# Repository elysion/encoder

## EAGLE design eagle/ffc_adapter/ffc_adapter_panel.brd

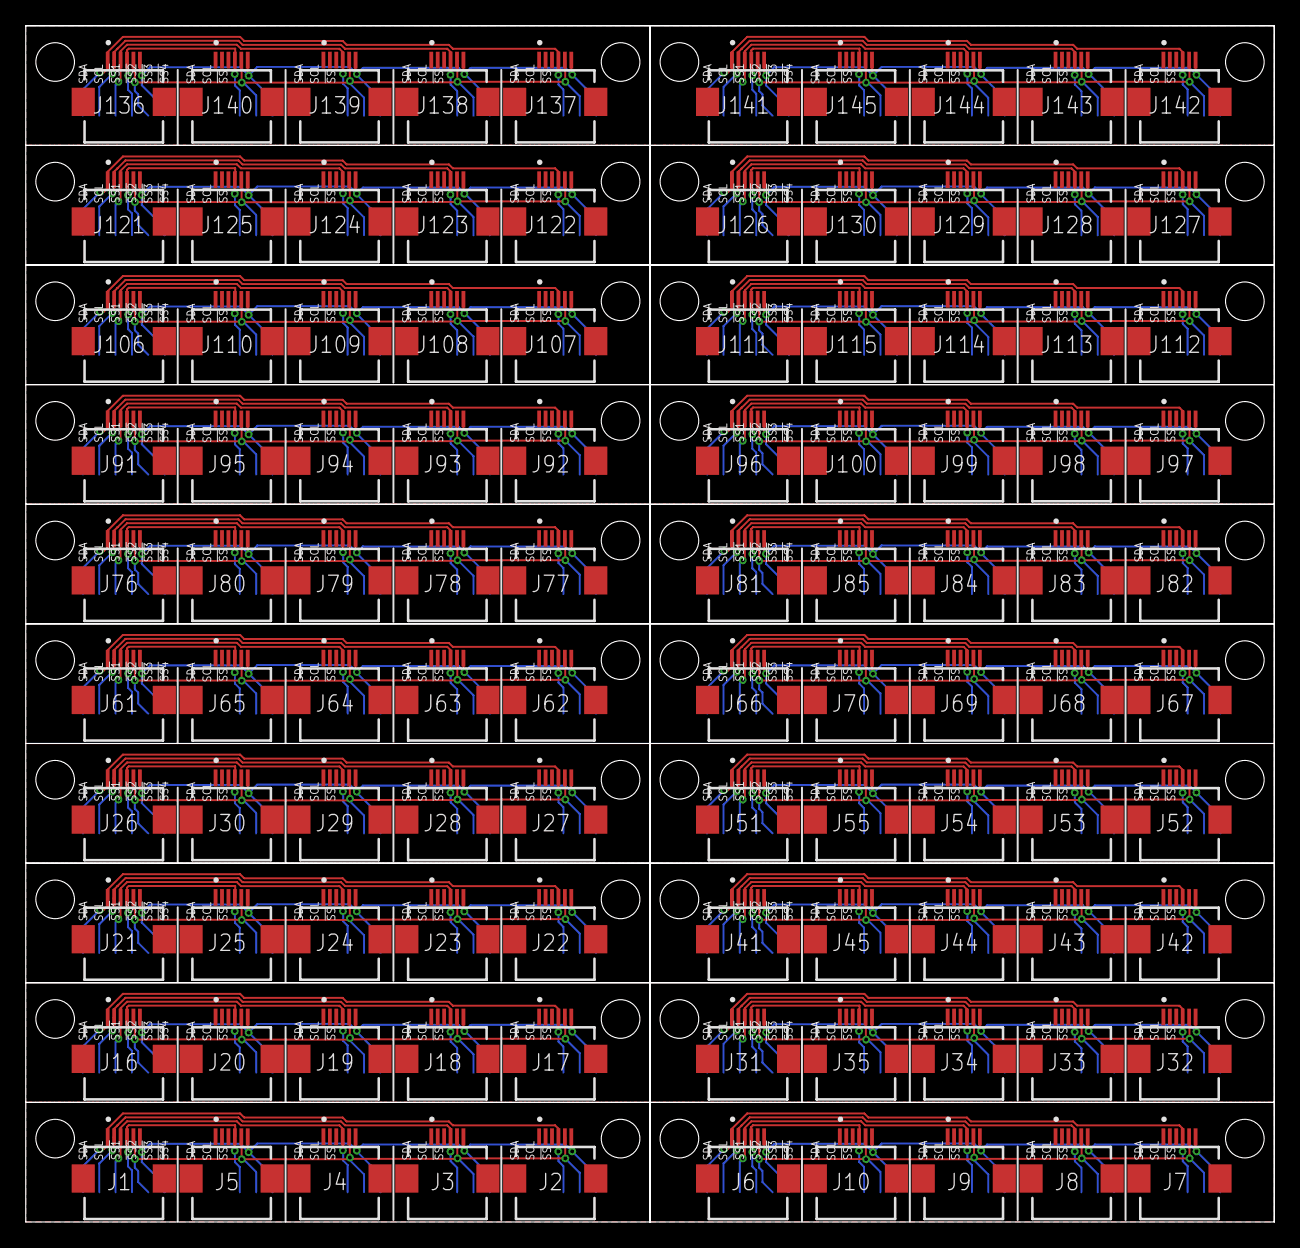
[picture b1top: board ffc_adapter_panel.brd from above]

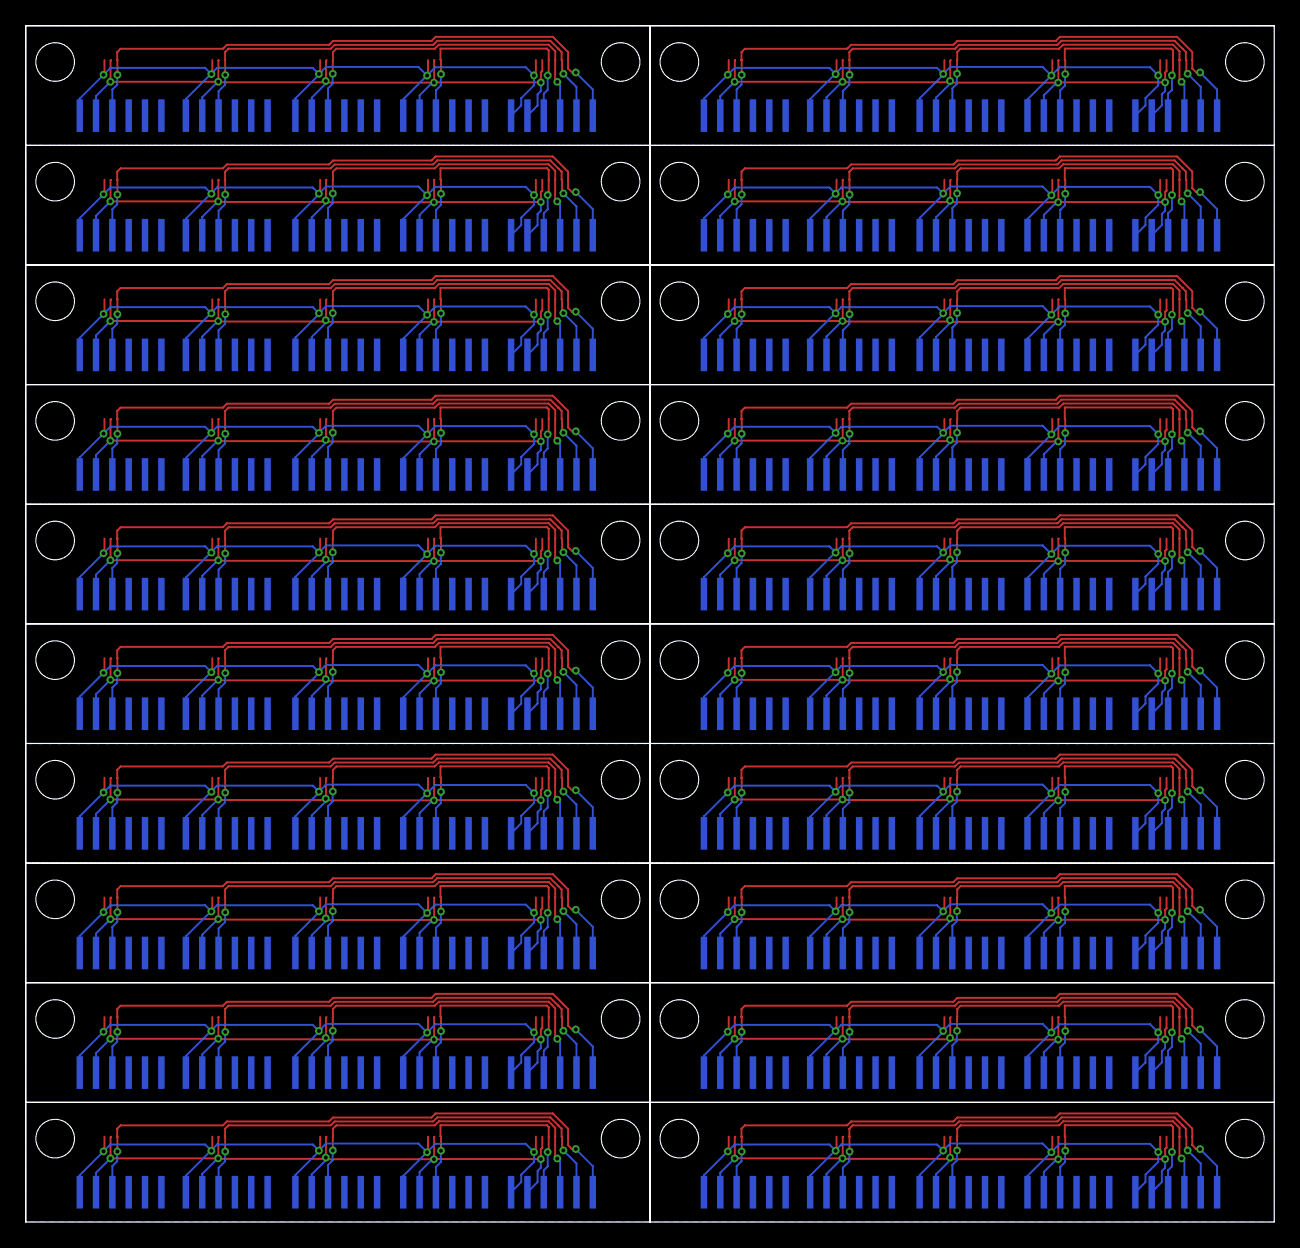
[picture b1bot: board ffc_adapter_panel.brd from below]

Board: 2 copper layers, 97.0 x 93.0 mm, 200 parts (100 on the bottom side), 120 nets.

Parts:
J1, J2, J3, J4, J5, J6, J7, J8, J9, J10, J16, J17, J18, J19, J20, J21, J22, J23, J24, J25, J26, J27, J28, J29, J30, J31, J32, J33, J34, J35, J41, J42, J43, J44, J45, J51, J52, J53, J54, J55, J61, J62, J63, J64, J65, J66, J67, J68, J69, J70, J76, J77, J78, J79, J80, J81, J82, J83, J84, J85, J91, J92, J93, J94, J95, J96, J97, J98, J99, J100, J106, J107, J108, J109, J110, J111, J112, J113, J114, J115, J121, J122, J123, J124, J125, J126, J127, J128, J129, J130, J136, J137, J138, J139, J140, J141, J142, J143, J144, J145: FH12-6S-0.5SH(55); FH12-6S-0.5SH(55)_1
U$1, U$2, U$3, U$4, U$5, U$6, U$7, U$8, U$9, U$10, U$16, U$17, U$18, U$19, U$20, U$21, U$22, U$23, U$24, U$25, U$26, U$27, U$28, U$29, U$30, U$31, U$32, U$33, U$34, U$35, U$41, U$42, U$43, U$44, U$45, U$51, U$52, U$53, U$54, U$55, U$61, U$62, U$63, U$64, U$65, U$66, U$67, U$68, U$69, U$70, U$76, U$77, U$78, U$79, U$80, U$81, U$82, U$83, U$84, U$85, U$91, U$92, U$93, U$94, U$95, U$96, U$97, U$98, U$99, U$100, U$106, U$107, U$108, U$109, U$110, U$111, U$112, U$113, U$114, U$115, U$121, U$122, U$123, U$124, U$125, U$126, U$127, U$128, U$129, U$130, U$136, U$137, U$138, U$139, U$140, U$141, U$142, U$143, U$144, U$145: 6PIN_SOLDER_PAD

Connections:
!SS1: J1.4, J5.4, U$4.P$3, U$5.P$3
!SS2: J1.3, J4.4, U$3.P$3, U$4.P$4
!SS3: J1.2, J3.4, U$2.P$3, U$4.P$5
!SS4: J1.1, J2.4, U$1.P$3, U$4.P$6
!SS5: J6.4, J10.4, U$6.P$3, U$10.P$3
!SS6: J6.3, J9.4, U$6.P$4, U$9.P$3
!SS7: J6.2, J8.4, U$6.P$5, U$8.P$3
!SS8: J6.1, J7.4, U$6.P$6, U$7.P$3
!SS13: J16.4, J20.4, U$16.P$3, U$20.P$3
!SS14: J16.3, J19.4, U$16.P$4, U$19.P$3
!SS15: J16.2, J18.4, U$16.P$5, U$18.P$3
!SS16: J16.1, J17.4, U$16.P$6, U$17.P$3
!SS17: J21.4, J25.4, U$21.P$3, U$25.P$3
!SS18: J21.3, J24.4, U$21.P$4, U$24.P$3
!SS19: J21.2, J23.4, U$21.P$5, U$23.P$3
!SS20: J21.1, J22.4, U$21.P$6, U$22.P$3
!SS21: J26.4, J30.4, U$26.P$3, U$30.P$3
!SS22: J26.3, J29.4, U$26.P$4, U$29.P$3
!SS23: J26.2, J28.4, U$26.P$5, U$28.P$3
!SS24: J26.1, J27.4, U$26.P$6, U$27.P$3
!SS25: J31.4, J35.4, U$31.P$3, U$35.P$3
!SS26: J31.3, J34.4, U$31.P$4, U$34.P$3
!SS27: J31.2, J33.4, U$31.P$5, U$33.P$3
!SS28: J31.1, J32.4, U$31.P$6, U$32.P$3
!SS33: J41.4, J45.4, U$41.P$3, U$45.P$3
!SS34: J41.3, J44.4, U$41.P$4, U$44.P$3
!SS35: J41.2, J43.4, U$41.P$5, U$43.P$3
!SS36: J41.1, J42.4, U$41.P$6, U$42.P$3
!SS41: J51.4, J55.4, U$51.P$3, U$55.P$3
!SS42: J51.3, J54.4, U$51.P$4, U$54.P$3
!SS43: J51.2, J53.4, U$51.P$5, U$53.P$3
!SS44: J51.1, J52.4, U$51.P$6, U$52.P$3
!SS49: J61.4, J65.4, U$61.P$3, U$65.P$3
!SS50: J61.3, J64.4, U$61.P$4, U$64.P$3
!SS51: J61.2, J63.4, U$61.P$5, U$63.P$3
!SS52: J61.1, J62.4, U$61.P$6, U$62.P$3
!SS53: J66.4, J70.4, U$66.P$3, U$70.P$3
!SS54: J66.3, J69.4, U$66.P$4, U$69.P$3
!SS55: J66.2, J68.4, U$66.P$5, U$68.P$3
!SS56: J66.1, J67.4, U$66.P$6, U$67.P$3
!SS61: J76.4, J80.4, U$76.P$3, U$80.P$3
!SS62: J76.3, J79.4, U$76.P$4, U$79.P$3
!SS63: J76.2, J78.4, U$76.P$5, U$78.P$3
!SS64: J76.1, J77.4, U$76.P$6, U$77.P$3
!SS65: J81.4, J85.4, U$81.P$3, U$85.P$3
!SS66: J81.3, J84.4, U$81.P$4, U$84.P$3
!SS67: J81.2, J83.4, U$81.P$5, U$83.P$3
!SS68: J81.1, J82.4, U$81.P$6, U$82.P$3
!SS73: J91.4, J95.4, U$91.P$3, U$95.P$3
!SS74: J91.3, J94.4, U$91.P$4, U$94.P$3
!SS75: J91.2, J93.4, U$91.P$5, U$93.P$3
!SS76: J91.1, J92.4, U$91.P$6, U$92.P$3
!SS77: J96.4, J100.4, U$96.P$3, U$100.P$3
!SS78: J96.3, J99.4, U$96.P$4, U$99.P$3
!SS79: J96.2, J98.4, U$96.P$5, U$98.P$3
!SS80: J96.1, J97.4, U$96.P$6, U$97.P$3
!SS85: J106.4, J110.4, U$106.P$3, U$110.P$3
!SS86: J106.3, J109.4, U$106.P$4, U$109.P$3
!SS87: J106.2, J108.4, U$106.P$5, U$108.P$3
!SS88: J106.1, J107.4, U$106.P$6, U$107.P$3
!SS89: J111.4, J115.4, U$111.P$3, U$115.P$3
!SS90: J111.3, J114.4, U$111.P$4, U$114.P$3
!SS91: J111.2, J113.4, U$111.P$5, U$113.P$3
!SS92: J111.1, J112.4, U$111.P$6, U$112.P$3
!SS97: J121.4, J125.4, U$121.P$3, U$125.P$3
!SS98: J121.3, J124.4, U$121.P$4, U$124.P$3
!SS99: J121.2, J123.4, U$121.P$5, U$123.P$3
!SS100: J121.1, J122.4, U$121.P$6, U$122.P$3
!SS101: J126.4, J130.4, U$126.P$3, U$130.P$3
!SS102: J126.3, J129.4, U$126.P$4, U$129.P$3
!SS103: J126.2, J128.4, U$126.P$5, U$128.P$3
!SS104: J126.1, J127.4, U$126.P$6, U$127.P$3
!SS109: J136.4, J140.4, U$136.P$3, U$140.P$3
!SS110: J136.3, J139.4, U$136.P$4, U$139.P$3
!SS111: J136.2, J138.4, U$136.P$5, U$138.P$3
!SS112: J136.1, J137.4, U$136.P$6, U$137.P$3
!SS113: J141.4, J145.4, U$141.P$3, U$145.P$3
!SS114: J141.3, J144.4, U$141.P$4, U$144.P$3
!SS115: J141.2, J143.4, U$141.P$5, U$143.P$3
!SS116: J141.1, J142.4, U$141.P$6, U$142.P$3
SCL: J1.5, J2.5, J3.5, J4.5, J5.5, U$1.P$2, U$2.P$2, U$3.P$2, U$4.P$2, U$5.P$2
SCL1: J6.5, J7.5, J8.5, J9.5, J10.5, U$6.P$2, U$7.P$2, U$8.P$2, U$9.P$2, U$10.P$2
SCL3: J16.5, J17.5, J18.5, J19.5, J20.5, U$16.P$2, U$17.P$2, U$18.P$2, U$19.P$2, U$20.P$2
SCL4: J21.5, J22.5, J23.5, J24.5, J25.5, U$21.P$2, U$22.P$2, U$23.P$2, U$24.P$2, U$25.P$2
SCL5: J26.5, J27.5, J28.5, J29.5, J30.5, U$26.P$2, U$27.P$2, U$28.P$2, U$29.P$2, U$30.P$2
SCL6: J31.5, J32.5, J33.5, J34.5, J35.5, U$31.P$2, U$32.P$2, U$33.P$2, U$34.P$2, U$35.P$2
SCL8: J41.5, J42.5, J43.5, J44.5, J45.5, U$41.P$2, U$42.P$2, U$43.P$2, U$44.P$2, U$45.P$2
SCL10: J51.5, J52.5, J53.5, J54.5, J55.5, U$51.P$2, U$52.P$2, U$53.P$2, U$54.P$2, U$55.P$2
SCL12: J61.5, J62.5, J63.5, J64.5, J65.5, U$61.P$2, U$62.P$2, U$63.P$2, U$64.P$2, U$65.P$2
SCL13: J66.5, J67.5, J68.5, J69.5, J70.5, U$66.P$2, U$67.P$2, U$68.P$2, U$69.P$2, U$70.P$2
SCL15: J76.5, J77.5, J78.5, J79.5, J80.5, U$76.P$2, U$77.P$2, U$78.P$2, U$79.P$2, U$80.P$2
SCL16: J81.5, J82.5, J83.5, J84.5, J85.5, U$81.P$2, U$82.P$2, U$83.P$2, U$84.P$2, U$85.P$2
SCL18: J91.5, J92.5, J93.5, J94.5, J95.5, U$91.P$2, U$92.P$2, U$93.P$2, U$94.P$2, U$95.P$2
SCL19: J96.5, J97.5, J98.5, J99.5, J100.5, U$96.P$2, U$97.P$2, U$98.P$2, U$99.P$2, U$100.P$2
SCL21: J106.5, J107.5, J108.5, J109.5, J110.5, U$106.P$2, U$107.P$2, U$108.P$2, U$109.P$2, U$110.P$2
SCL22: J111.5, J112.5, J113.5, J114.5, J115.5, U$111.P$2, U$112.P$2, U$113.P$2, U$114.P$2, U$115.P$2
SCL24: J121.5, J122.5, J123.5, J124.5, J125.5, U$121.P$2, U$122.P$2, U$123.P$2, U$124.P$2, U$125.P$2
SCL25: J126.5, J127.5, J128.5, J129.5, J130.5, U$126.P$2, U$127.P$2, U$128.P$2, U$129.P$2, U$130.P$2
SCL27: J136.5, J137.5, J138.5, J139.5, J140.5, U$136.P$2, U$137.P$2, U$138.P$2, U$139.P$2, U$140.P$2
SCL28: J141.5, J142.5, J143.5, J144.5, J145.5, U$141.P$2, U$142.P$2, U$143.P$2, U$144.P$2, U$145.P$2
SDA: J1.6, J2.6, J3.6, J4.6, J5.6, U$1.P$1, U$2.P$1, U$3.P$1, U$4.P$1, U$5.P$1
SDA1: J6.6, J7.6, J8.6, J9.6, J10.6, U$6.P$1, U$7.P$1, U$8.P$1, U$9.P$1, U$10.P$1
SDA3: J16.6, J17.6, J18.6, J19.6, J20.6, U$16.P$1, U$17.P$1, U$18.P$1, U$19.P$1, U$20.P$1
SDA4: J21.6, J22.6, J23.6, J24.6, J25.6, U$21.P$1, U$22.P$1, U$23.P$1, U$24.P$1, U$25.P$1
SDA5: J26.6, J27.6, J28.6, J29.6, J30.6, U$26.P$1, U$27.P$1, U$28.P$1, U$29.P$1, U$30.P$1
SDA6: J31.6, J32.6, J33.6, J34.6, J35.6, U$31.P$1, U$32.P$1, U$33.P$1, U$34.P$1, U$35.P$1
SDA8: J41.6, J42.6, J43.6, J44.6, J45.6, U$41.P$1, U$42.P$1, U$43.P$1, U$44.P$1, U$45.P$1
SDA10: J51.6, J52.6, J53.6, J54.6, J55.6, U$51.P$1, U$52.P$1, U$53.P$1, U$54.P$1, U$55.P$1
SDA12: J61.6, J62.6, J63.6, J64.6, J65.6, U$61.P$1, U$62.P$1, U$63.P$1, U$64.P$1, U$65.P$1
SDA13: J66.6, J67.6, J68.6, J69.6, J70.6, U$66.P$1, U$67.P$1, U$68.P$1, U$69.P$1, U$70.P$1
SDA15: J76.6, J77.6, J78.6, J79.6, J80.6, U$76.P$1, U$77.P$1, U$78.P$1, U$79.P$1, U$80.P$1
SDA16: J81.6, J82.6, J83.6, J84.6, J85.6, U$81.P$1, U$82.P$1, U$83.P$1, U$84.P$1, U$85.P$1
SDA18: J91.6, J92.6, J93.6, J94.6, J95.6, U$91.P$1, U$92.P$1, U$93.P$1, U$94.P$1, U$95.P$1
SDA19: J96.6, J97.6, J98.6, J99.6, J100.6, U$96.P$1, U$97.P$1, U$98.P$1, U$99.P$1, U$100.P$1
SDA21: J106.6, J107.6, J108.6, J109.6, J110.6, U$106.P$1, U$107.P$1, U$108.P$1, U$109.P$1, U$110.P$1
SDA22: J111.6, J112.6, J113.6, J114.6, J115.6, U$111.P$1, U$112.P$1, U$113.P$1, U$114.P$1, U$115.P$1
SDA24: J121.6, J122.6, J123.6, J124.6, J125.6, U$121.P$1, U$122.P$1, U$123.P$1, U$124.P$1, U$125.P$1
SDA25: J126.6, J127.6, J128.6, J129.6, J130.6, U$126.P$1, U$127.P$1, U$128.P$1, U$129.P$1, U$130.P$1
SDA27: J136.6, J137.6, J138.6, J139.6, J140.6, U$136.P$1, U$137.P$1, U$138.P$1, U$139.P$1, U$140.P$1
SDA28: J141.6, J142.6, J143.6, J144.6, J145.6, U$141.P$1, U$142.P$1, U$143.P$1, U$144.P$1, U$145.P$1

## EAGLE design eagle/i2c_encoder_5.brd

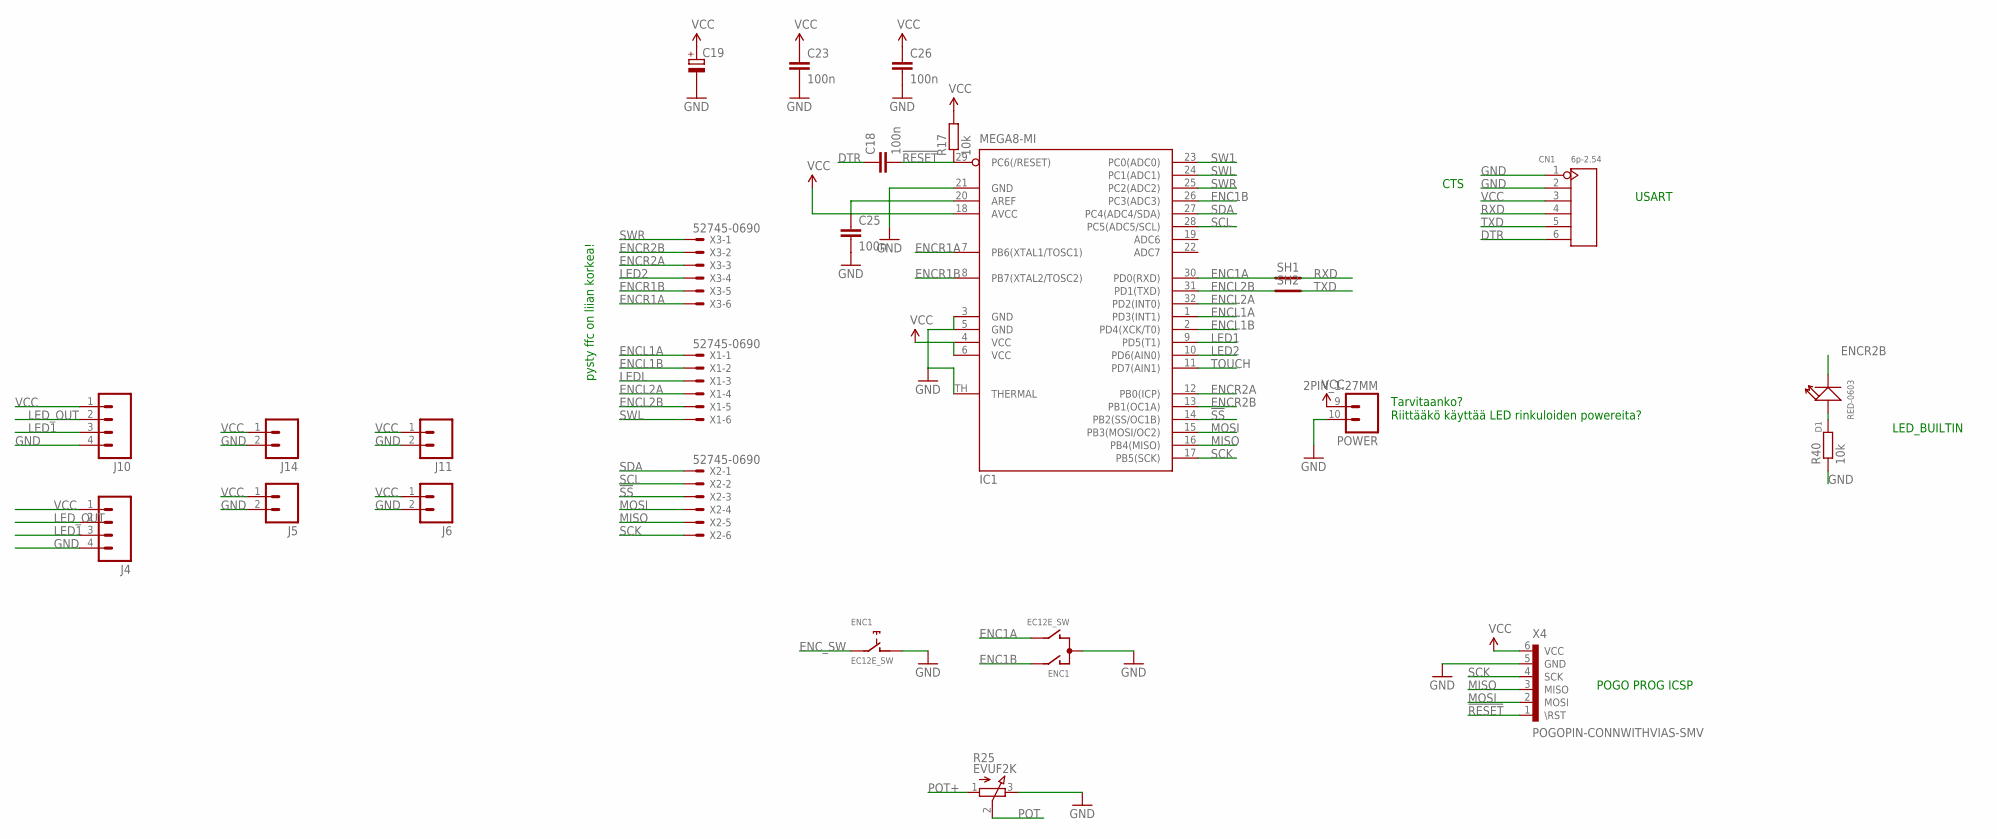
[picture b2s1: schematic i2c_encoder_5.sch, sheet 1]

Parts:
C18, C23, C25, C26: 100n; 0603-CAP
C19: CPOL-EUC; PANASONIC_C
CN1: 6p-2.54; H6-2.54
D1: RED-0603; LED-0603
ENC1: EC12E_SW; ALPS_EC12E_SW
IC1: MEGA8-MI; MLF32-TH
J4, J10: M04NO_SILK_ALL_ROUND; 1X04_NO_SILK_ALL_ROUND
J5, J6, J11, J14: M021X02_NO_SILK; 1X02_NO_SILK
POWER: 2PIN_1.27MM; 1X02_1.27MM_NO_SILK
R17, R40: 10k; R0603
R25: EVUF2K; EVUFXK
SH1, SH2: SHORT; SHORT_TOP_8MIL
X1, X2, X3: 52745-0690
X4: POGOPIN-CONNWITHVIAS-SMV; POGOPROG-CONN-OH-SMALLERVIAS

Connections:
!RESET: C18.2, IC1.29 (PC6(/RESET)), R17.1, X4.1 (\RST)
!SS: IC1.14 (PB2(SS/OC1B)), X2.3; also elsewhere on the board
AREF: C25.1, IC1.20 (AREF)
DTR: C18.1, CN1.6
ENC1A: ENC1.B, IC1.30 (PD0(RXD)), SH1.P$1; also elsewhere on the board
ENC1B: ENC1.A, IC1.26 (PC3(ADC3)); also elsewhere on the board
ENCL1A: IC1.1 (PD3(INT1)), X1.1; also elsewhere on the board
ENCL1B: IC1.2 (PD4(XCK/T0)), X1.2; also elsewhere on the board
ENCL2A: IC1.32 (PD2(INT0)), X1.4; also elsewhere on the board
ENCL2B: IC1.31 (PD1(TXD)), SH2.P$1, X1.5; also elsewhere on the board
ENCR1A: IC1.7 (PB6(XTAL1/TOSC1)), X3.6; also elsewhere on the board
ENCR1B: IC1.8 (PB7(XTAL2/TOSC2)), X3.5; also elsewhere on the board
ENCR2A: IC1.12 (PB0(ICP)), X3.3; also elsewhere on the board
ENCR2B: D1.-, IC1.13 (PB1(OC1A)), X3.2; also elsewhere on the board
ENC_SW: ENC1.E (2); also elsewhere on the board
GND: C19.-, C23.2, C25.2, C26.2, CN1.1, CN1.2, ENC1.C, ENC1.D (1), IC1.3 (GND), IC1.5 (GND), IC1.21 (GND), IC1.TH (THERMAL), J4.4, J5.2, J6.2, J10.4, J11.2, J14.2, POWER.10 (2), R25.3 (E), R40.1, X4.5 (GND); also elsewhere on the board
LED1: IC1.9 (PD5(T1)), J4.3, J10.3; also elsewhere on the board
LED2: IC1.10 (PD6(AIN0)), X3.4; also elsewhere on the board
LEDL: X1.3; also elsewhere on the board
LED_OUT: J4.2, J10.2; also elsewhere on the board
MISO: IC1.16 (PB4(MISO)), X2.5, X4.3 (MISO); also elsewhere on the board
MOSI: IC1.15 (PB3(MOSI/OC2)), X2.4, X4.2 (MOSI); also elsewhere on the board
unnamed: D1.+, R40.2
POT: R25.2 (S); also elsewhere on the board
POT+: R25.1 (A); also elsewhere on the board
RXD: CN1.4, SH1.P$2
SCK: IC1.17 (PB5(SCK)), X2.6, X4.4 (SCK); also elsewhere on the board
SCL: IC1.28 (PC5(ADC5/SCL)), X2.2; also elsewhere on the board
SDA: IC1.27 (PC4(ADC4/SDA)), X2.1; also elsewhere on the board
SW1: IC1.23 (PC0(ADC0)); also elsewhere on the board
SWL: IC1.24 (PC1(ADC1)), X1.6; also elsewhere on the board
SWR: IC1.25 (PC2(ADC2)), X3.1; also elsewhere on the board
TOUCH: IC1.11 (PD7(AIN1)); also elsewhere on the board
TXD: CN1.5, SH2.P$2
VCC: C19.+, C23.1, C26.1, CN1.3, IC1.4 (VCC), IC1.6 (VCC), IC1.18 (AVCC), J4.1, J5.1, J6.1, J10.1, J11.1, J14.1, POWER.9 (1), R17.2, X4.6 (VCC); also elsewhere on the board

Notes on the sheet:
CTS
Tarvitaanko? Riittääkö käyttää LED rinkuloiden powereita?
USART
POGO PROG ICSP
pysty ffc on liian korkea!
LED_BUILTIN

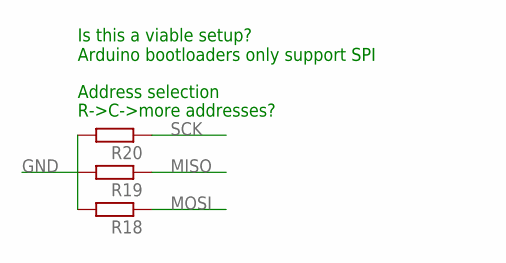
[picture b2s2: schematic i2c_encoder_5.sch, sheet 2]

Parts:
R18, R19, R20: R-EU_R0603; R0603

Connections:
GND: R18.2, R19.2, R20.2; also elsewhere on the board
MISO: R19.1; also elsewhere on the board
MOSI: R18.1; also elsewhere on the board
SCK: R20.1; also elsewhere on the board

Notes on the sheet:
Address selection
R->C->more addresses?
Is this a viable setup? Arduino bootloaders only support SPI

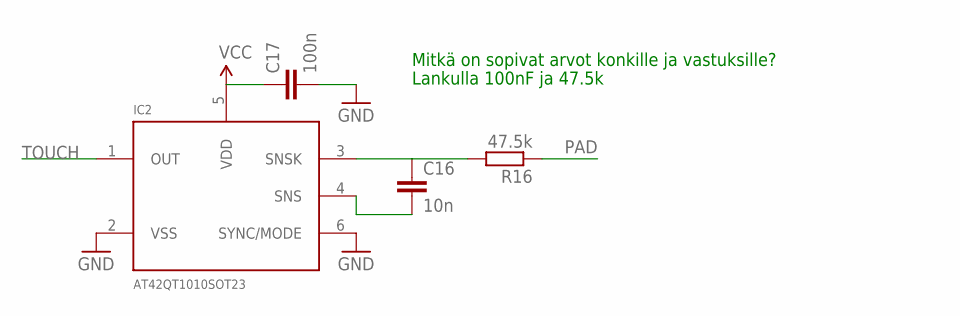
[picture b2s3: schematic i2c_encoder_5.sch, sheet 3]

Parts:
C16: 10n; 0603-CAP
C17: 100n; 0603-CAP
IC2: AT42QT1010SOT23; SOT23-6
R16: 47.5k; R0603

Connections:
GND: C17.2, IC2.2 (VSS), IC2.6 (SYNC/MODE); also elsewhere on the board
unnamed: C16.1, IC2.3 (SNSK), R16.2
unnamed: C16.2, IC2.4 (SNS)
PAD: R16.1
TOUCH: IC2.1 (OUT); also elsewhere on the board
VCC: C17.1, IC2.5 (VDD); also elsewhere on the board

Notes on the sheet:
Mitkä on sopivat arvot konkille ja vastuksille?
Lankulla 100nF ja 47.5k

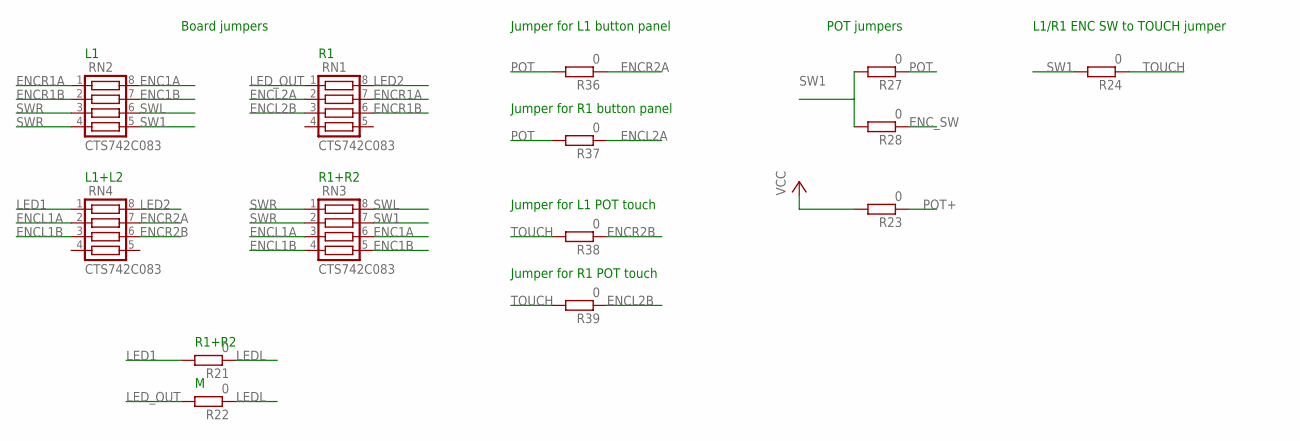
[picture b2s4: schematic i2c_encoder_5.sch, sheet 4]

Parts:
R21, R22, R23, R24, R27, R28, R36, R37, R38, R39: 0; R0603
RN1, RN2, RN3, RN4: CTS742C083

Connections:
ENC1A: RN2.8, RN3.6; also elsewhere on the board
ENC1B: RN2.7, RN3.5; also elsewhere on the board
ENCL1A: RN3.3, RN4.2; also elsewhere on the board
ENCL1B: RN3.4, RN4.3; also elsewhere on the board
ENCL2A: R37.1, RN1.2; also elsewhere on the board
ENCL2B: R39.1, RN1.3; also elsewhere on the board
ENCR1A: RN1.7, RN2.1; also elsewhere on the board
ENCR1B: RN1.6, RN2.2; also elsewhere on the board
ENCR2A: R36.1, RN4.7; also elsewhere on the board
ENCR2B: R38.1, RN4.6; also elsewhere on the board
ENC_SW: R28.1; also elsewhere on the board
LED1: R21.2, RN4.1; also elsewhere on the board
LED2: RN1.8, RN4.8; also elsewhere on the board
LEDL: R21.1, R22.1; also elsewhere on the board
LED_OUT: R22.2, RN1.1; also elsewhere on the board
POT: R27.1, R36.2, R37.2; also elsewhere on the board
POT+: R23.1; also elsewhere on the board
SW1: R24.2, R27.2, R28.2, RN2.5, RN3.7; also elsewhere on the board
SWL: RN2.6, RN3.8; also elsewhere on the board
SWR: RN2.3, RN2.4, RN3.1, RN3.2; also elsewhere on the board
TOUCH: R24.1, R38.2, R39.2; also elsewhere on the board
VCC: R23.2; also elsewhere on the board

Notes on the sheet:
R1+R2
L1/R1 ENC SW to TOUCH jumper
Jumper for L1 button panel
Jumper for R1 button panel
Jumper for L1 POT touch
Jumper for R1 POT touch
L1+L2
Board jumpers
POT jumpers

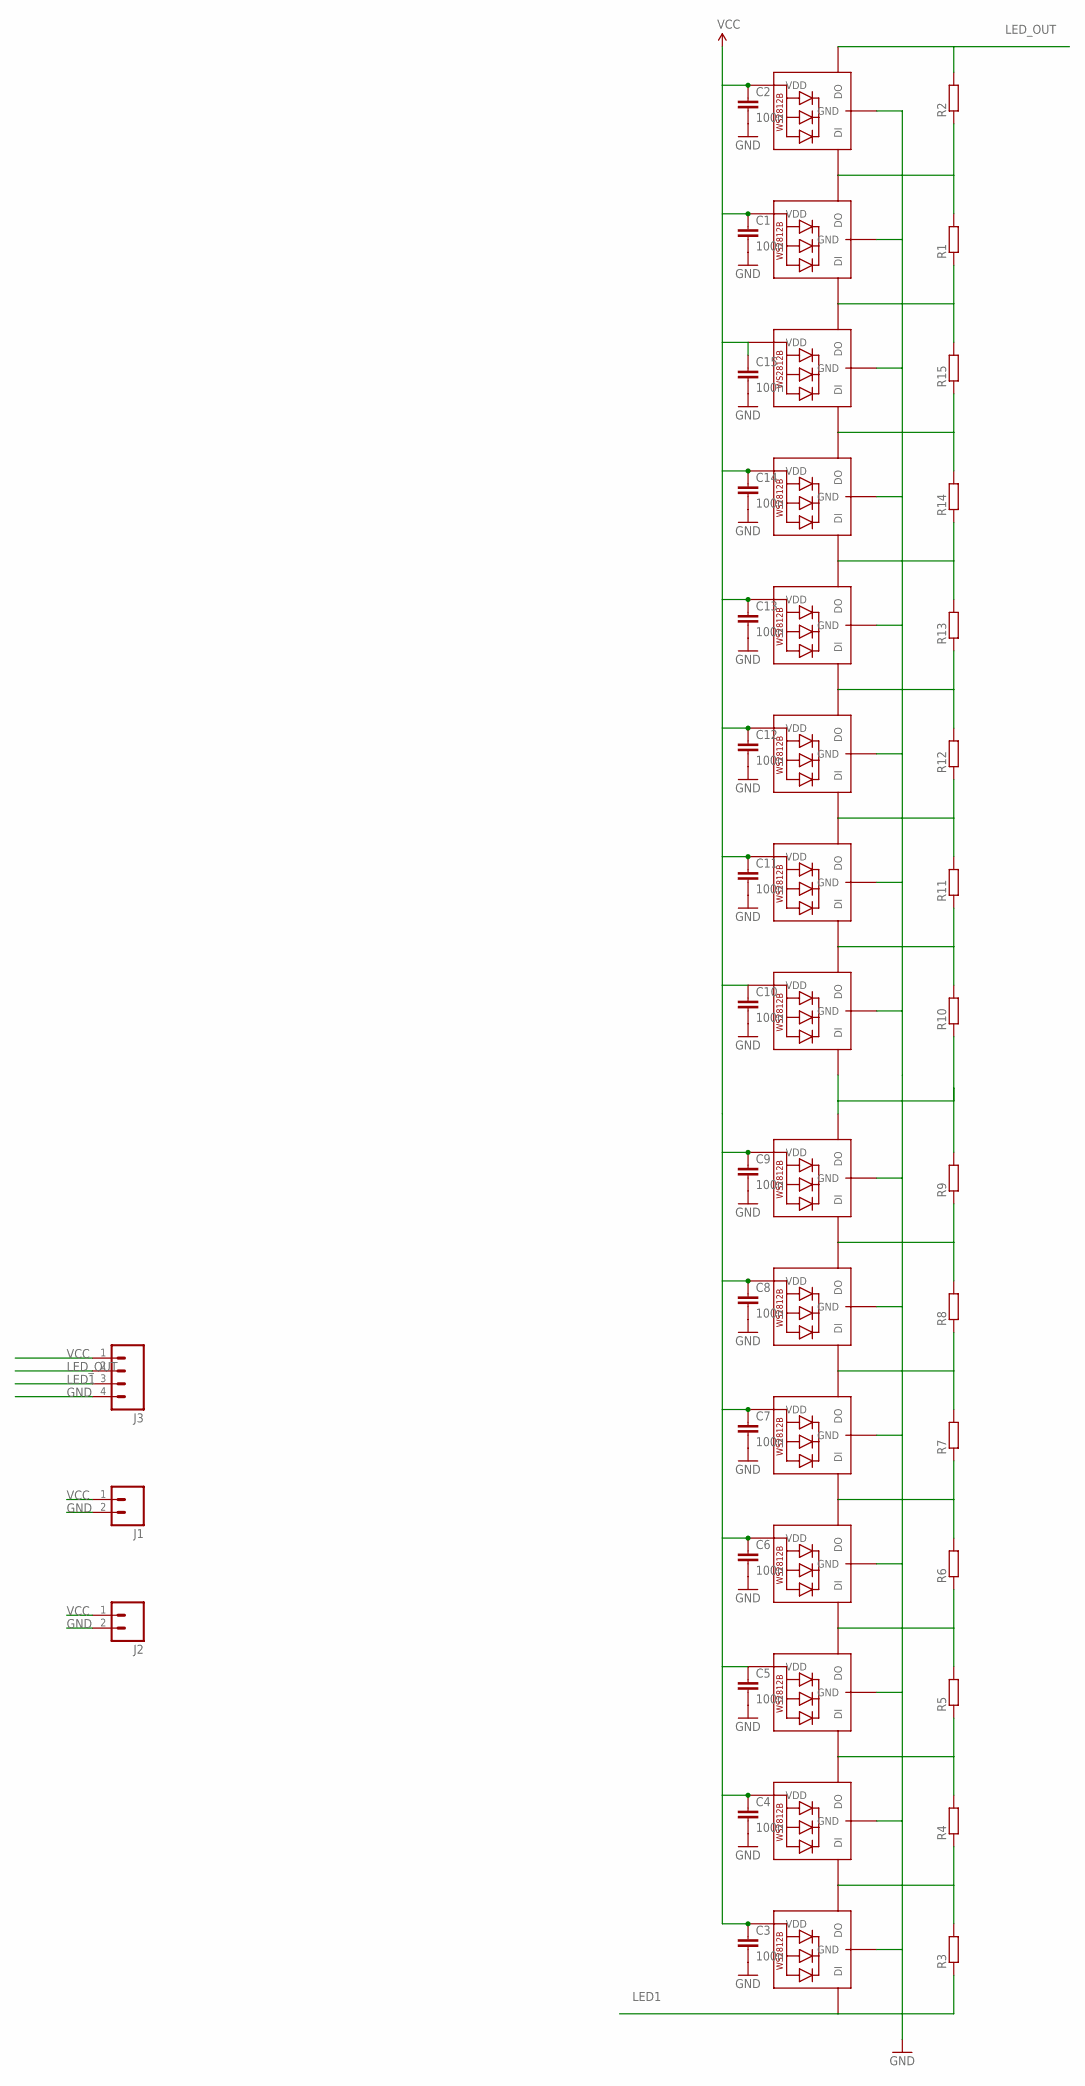
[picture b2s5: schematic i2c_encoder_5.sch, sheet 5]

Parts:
C1, C2, C3, C4, C5, C6, C7, C8, C9, C10, C11, C12, C13, C14, C15: 100n; 0603-CAP
J1, J2: M021X02_NO_SILK; 1X02_NO_SILK
J3: M04NO_SILK_ALL_ROUND; 1X04_NO_SILK_ALL_ROUND
LED1, LED2, LED3, LED4, LED5, LED6, LED7, LED8, LED9, LED10, LED11, LED12, LED13, LED14, LED15: WS2812B3535; LED3535
R1, R2, R3, R4, R5, R6, R7, R8, R9, R10, R11, R12, R13, R14, R15: R-EU_R0603; R0603

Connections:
GND: C1.2, C2.2, C3.2, C4.2, C5.2, C6.2, C7.2, C8.2, C9.2, C10.2, C11.2, C12.2, C13.2, C14.2, C15.2, J1.2, J2.2, J3.4, LED1.4 (GND), LED2.4 (GND), LED3.4 (GND), LED4.4 (GND), LED5.4 (GND), LED6.4 (GND), LED7.4 (GND), LED8.4 (GND), LED9.4 (GND), LED10.4 (GND), LED11.4 (GND), LED12.4 (GND), LED13.4 (GND), LED14.4 (GND), LED15.4 (GND); also elsewhere on the board
LED1: J3.3, LED1.1 (DI), R3.1; also elsewhere on the board
LED_OUT: J3.2, LED15.3 (DO), R2.2; also elsewhere on the board
unnamed: LED10.3 (DO), LED11.1 (DI), R12.2, R13.1
unnamed: LED11.3 (DO), LED12.1 (DI), R13.2, R14.1
unnamed: LED2.3 (DO), LED3.1 (DI), R4.2, R5.1
unnamed: LED13.3 (DO), LED14.1 (DI), R1.1, R15.2
unnamed: LED12.3 (DO), LED13.1 (DI), R14.2, R15.1
unnamed: LED8.3 (DO), LED9.1 (DI), R10.2, R11.1
unnamed: LED3.3 (DO), LED4.1 (DI), R5.2, R6.1
unnamed: LED14.3 (DO), LED15.1 (DI), R1.2, R2.1
unnamed: LED1.3 (DO), LED2.1 (DI), R3.2, R4.1
unnamed: LED4.3 (DO), LED5.1 (DI), R6.2, R7.1
unnamed: LED5.3 (DO), LED6.1 (DI), R7.2, R8.1
unnamed: LED6.3 (DO), LED7.1 (DI), R8.2, R9.1
unnamed: LED9.3 (DO), LED10.1 (DI), R11.2, R12.1
unnamed: LED7.3 (DO), LED8.1 (DI), R9.2, R10.1
VCC: C1.1, C2.1, C3.1, C4.1, C5.1, C6.1, C7.1, C8.1, C9.1, C10.1, C11.1, C12.1, C13.1, C14.1, C15.1, J1.1, J2.1, J3.1, LED1.2 (VDD), LED2.2 (VDD), LED3.2 (VDD), LED4.2 (VDD), LED5.2 (VDD), LED6.2 (VDD), LED7.2 (VDD), LED8.2 (VDD), LED9.2 (VDD), LED10.2 (VDD), LED11.2 (VDD), LED12.2 (VDD), LED13.2 (VDD), LED14.2 (VDD), LED15.2 (VDD); also elsewhere on the board

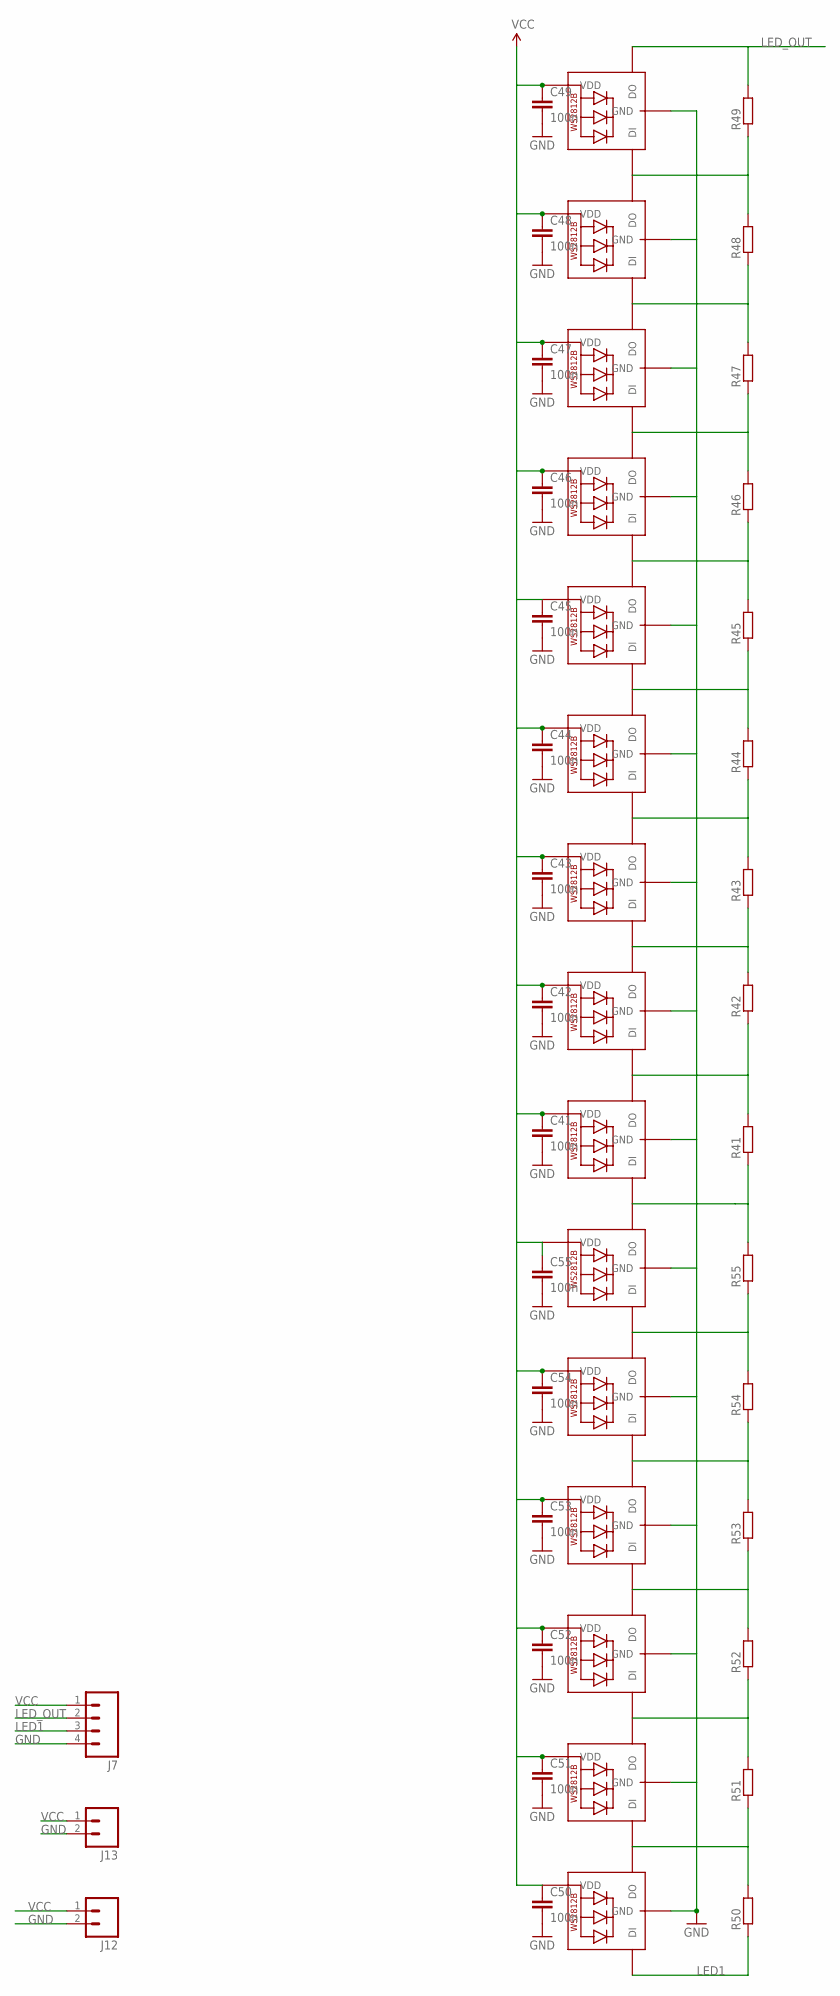
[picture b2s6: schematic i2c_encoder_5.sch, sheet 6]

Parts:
C41, C42, C43, C44, C45, C46, C47, C48, C49, C50, C51, C52, C53, C54, C55: 100n; 0603-CAP
J7: M04NO_SILK_ALL_ROUND; 1X04_NO_SILK_ALL_ROUND
J12, J13: M021X02_NO_SILK; 1X02_NO_SILK
LED31, LED32, LED33, LED34, LED35, LED36, LED37, LED38, LED39, LED40, LED41, LED42, LED43, LED44, LED45: WS2812B3535; LED3535
R41, R42, R43, R44, R45, R46, R47, R48, R49, R50, R51, R52, R53, R54, R55: R-EU_R0603; R0603

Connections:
GND: C41.2, C42.2, C43.2, C44.2, C45.2, C46.2, C47.2, C48.2, C49.2, C50.2, C51.2, C52.2, C53.2, C54.2, C55.2, J7.4, J12.2, J13.2, LED31.4 (GND), LED32.4 (GND), LED33.4 (GND), LED34.4 (GND), LED35.4 (GND), LED36.4 (GND), LED37.4 (GND), LED38.4 (GND), LED39.4 (GND), LED40.4 (GND), LED41.4 (GND), LED42.4 (GND), LED43.4 (GND), LED44.4 (GND), LED45.4 (GND); also elsewhere on the board
LED1: J7.3, LED31.1 (DI), R50.1; also elsewhere on the board
LED_OUT: J7.2, LED45.3 (DO), R49.2; also elsewhere on the board
unnamed: LED37.3 (DO), LED38.1 (DI), R41.2, R42.1
unnamed: LED38.3 (DO), LED39.1 (DI), R42.2, R43.1
unnamed: LED39.3 (DO), LED40.1 (DI), R43.2, R44.1
unnamed: LED42.3 (DO), LED43.1 (DI), R46.2, R47.1
unnamed: LED43.3 (DO), LED44.1 (DI), R47.2, R48.1
unnamed: LED44.3 (DO), LED45.1 (DI), R48.2, R49.1
unnamed: LED32.3 (DO), LED33.1 (DI), R51.2, R52.1
unnamed: LED33.3 (DO), LED34.1 (DI), R52.2, R53.1
unnamed: LED34.3 (DO), LED35.1 (DI), R53.2, R54.1
unnamed: LED35.3 (DO), LED36.1 (DI), R54.2, R55.1
unnamed: LED31.3 (DO), LED32.1 (DI), R50.2, R51.1
unnamed: LED40.3 (DO), LED41.1 (DI), R44.2, R45.1
unnamed: LED41.3 (DO), LED42.1 (DI), R45.2, R46.1
unnamed: LED36.3 (DO), LED37.1 (DI), R41.1, R55.2
VCC: C41.1, C42.1, C43.1, C44.1, C45.1, C46.1, C47.1, C48.1, C49.1, C50.1, C51.1, C52.1, C53.1, C54.1, C55.1, J7.1, J12.1, J13.1, LED31.2 (VDD), LED32.2 (VDD), LED33.2 (VDD), LED34.2 (VDD), LED35.2 (VDD), LED36.2 (VDD), LED37.2 (VDD), LED38.2 (VDD), LED39.2 (VDD), LED40.2 (VDD), LED41.2 (VDD), LED42.2 (VDD), LED43.2 (VDD), LED44.2 (VDD), LED45.2 (VDD); also elsewhere on the board

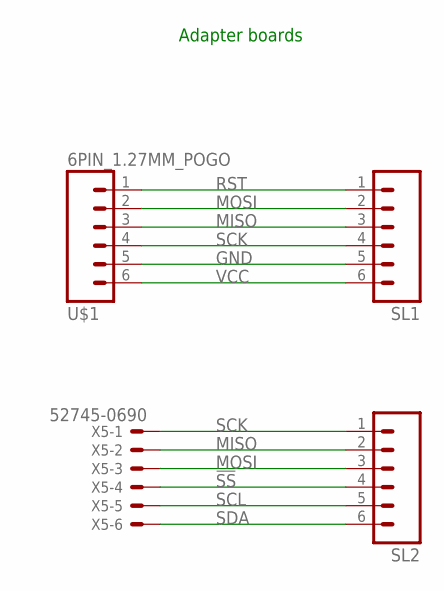
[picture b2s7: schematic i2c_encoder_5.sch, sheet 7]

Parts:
SL1, SL2: M06; 06P
U$1: 6PIN_1.27MM_POGO; 1X06-1.27MM_POGO
X5: 52745-0690

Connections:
!SS: SL2.4, X5.4; also elsewhere on the board
GND: SL1.5, U$1.5; also elsewhere on the board
MISO: SL1.3, SL2.2, U$1.3, X5.2; also elsewhere on the board
MOSI: SL1.2, SL2.3, U$1.2, X5.3; also elsewhere on the board
RST: SL1.1, U$1.1
SCK: SL1.4, SL2.1, U$1.4, X5.1; also elsewhere on the board
SCL: SL2.5, X5.5; also elsewhere on the board
SDA: SL2.6, X5.6; also elsewhere on the board
VCC: SL1.6, U$1.6; also elsewhere on the board

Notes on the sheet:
Adapter boards

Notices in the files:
parts and their libraries:
edge: Licensing: Creative Commons ShareAlike 4.0 International - https://creativecommons.org/licenses/by-sa/4.0
